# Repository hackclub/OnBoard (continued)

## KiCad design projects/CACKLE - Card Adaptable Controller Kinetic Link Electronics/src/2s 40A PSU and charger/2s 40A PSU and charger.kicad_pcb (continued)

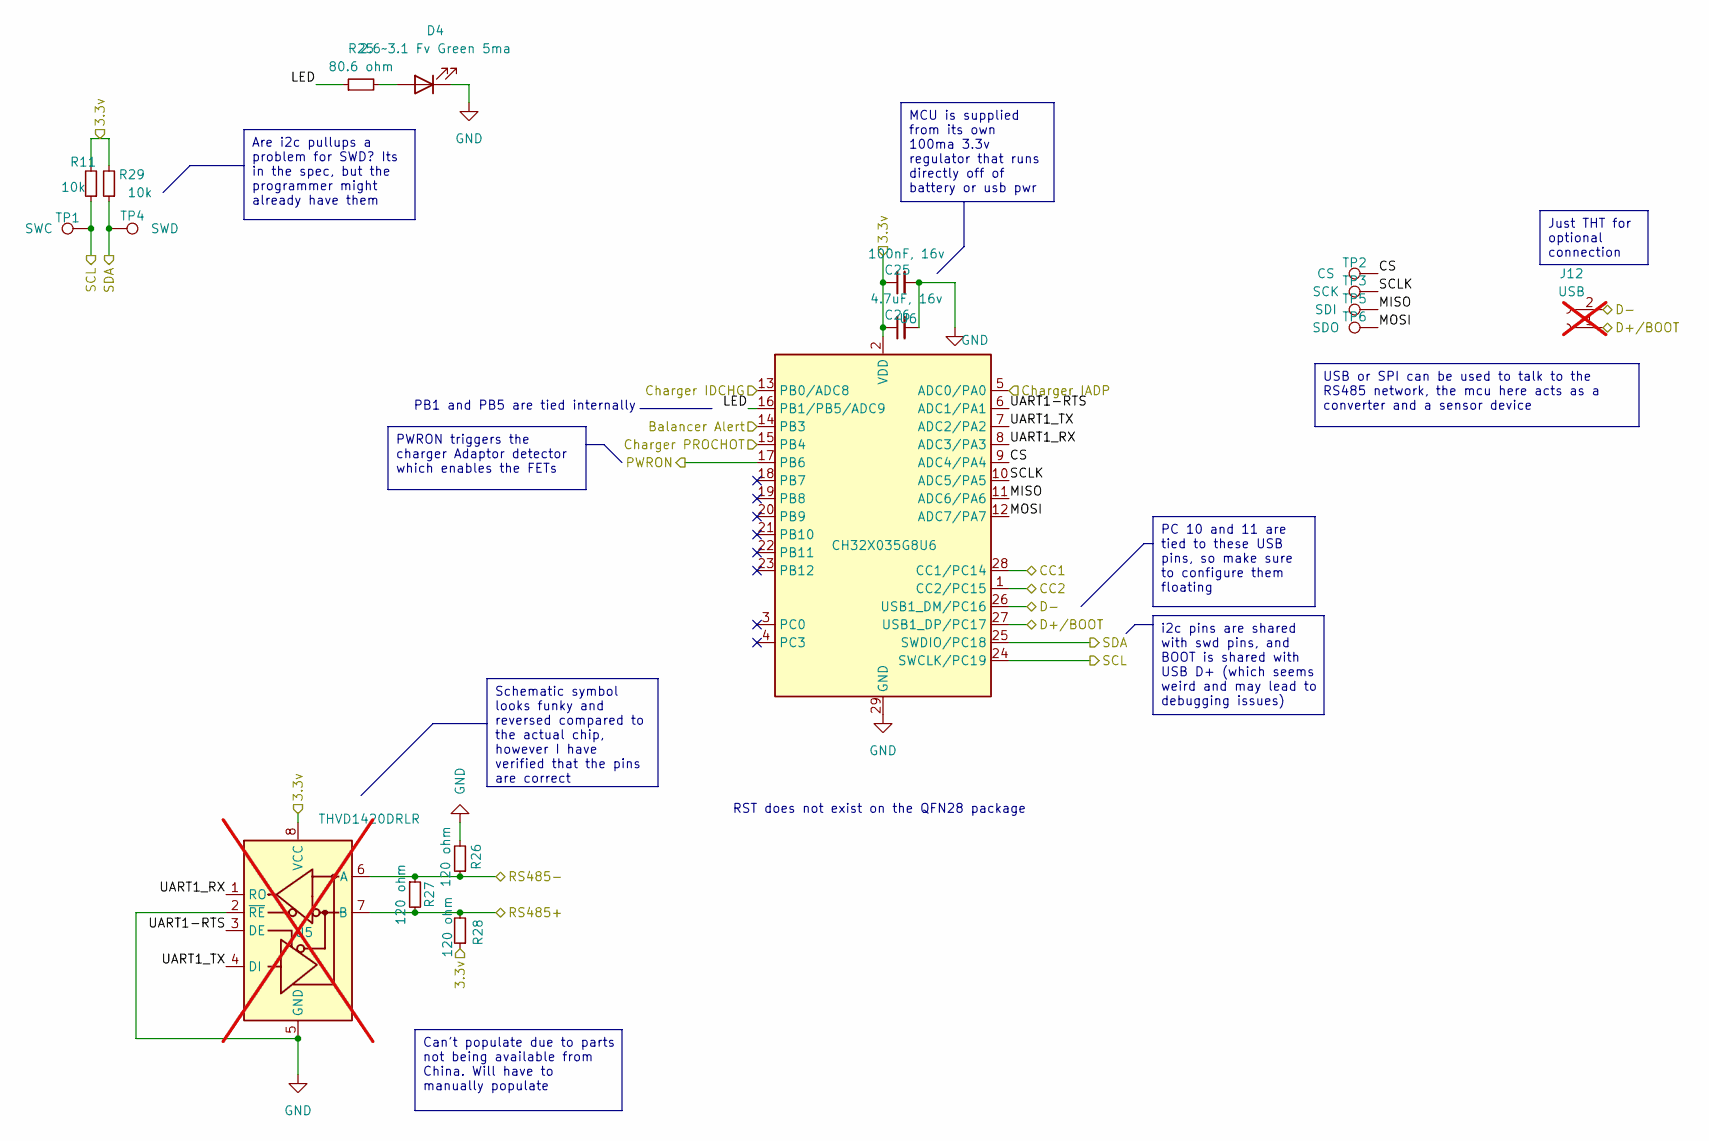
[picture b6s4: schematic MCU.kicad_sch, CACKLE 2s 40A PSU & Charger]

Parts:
C25: 100nF, 16v; C_0402_1005Metric; LCSC C1525
C26: 4.7uF, 16v; C_0603_1608Metric; LCSC C19666
D4: 2.6~3.1 Fv Green 5ma; LED_0603_1608Metric_Pad1.05x0.95mm_HandSolder; LCSC C3028858
J12: USB; PinHeader_1x02_P1.27mm_Vertical; not fitted
R11, R29: 10k; R_0402_1005Metric; LCSC C25744
R25: 80.6 ohm; R_0402_1005Metric; LCSC C185392
R26, R27, R28: 120 ohm; R_0402_1005Metric; LCSC C25079
TP1: SWC; TestPoint_Pad_D1.0mm
TP2: CS; TestPoint_Pad_D1.0mm
TP3: SCK; TestPoint_Pad_D1.0mm
TP4: SWD; TestPoint_Pad_D1.0mm
TP5: SDI; TestPoint_Pad_D1.0mm
TP6: SDO; TestPoint_Pad_D1.0mm
U5: THVD1420DRLR; SOT-583-8; not fitted
U6: CH32X035G8U6; QFN-28-1EP_4x4mm_P0.4mm_EP2.8x2.8mm; LCSC C7437027

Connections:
/Battery Balancer/Balancer Alert: U6.14 (PB3); also elsewhere on the board
/Battery Charger/Charger IADP: U6.5 (ADC0/PA0); also elsewhere on the board
/Battery Charger/Charger IDCHG: U6.13 (PB0/ADC8); also elsewhere on the board
/Battery Charger/Charger PROCHOT: U6.15 (PB4); also elsewhere on the board
/Battery Charger/MCU3.3v: C25.1, C26.1, R11.2, R28.1, R29.2, U5.8 (VCC), U6.2 (VDD); also elsewhere on the board
/Battery Charger/PWRON: U6.17 (PB6); also elsewhere on the board
/Connectors/CC1: U6.28 (CC1/PC14); also elsewhere on the board
/Connectors/CC2: U6.1 (CC2/PC15); also elsewhere on the board
/Connectors/D+: J12.1, U6.27 (USB1_DP/PC17); also elsewhere on the board
/Connectors/D-: J12.2, U6.26 (USB1_DM/PC16); also elsewhere on the board
/Connectors/RS485+: R27.2, R28.2, U5.7 (B); also elsewhere on the board
/Connectors/RS485-: R26.1, R27.1, U5.6 (A); also elsewhere on the board
/MCU/CS: TP2.1, U6.9 (ADC4/PA4)
/MCU/LED: R25.1, U6.16 (PB1/PB5/ADC9)
/MCU/MISO: TP5.1, U6.11 (ADC6/PA6)
/MCU/MOSI: TP6.1, U6.12 (ADC7/PA7)
/MCU/SCLK: TP3.1, U6.10 (ADC5/PA5)
/MCU/UART1-RTS: U5.3 (DE), U6.6 (ADC1/PA1)
/MCU/UART1_RX: U5.1 (RO), U6.8 (ADC3/PA3)
/MCU/UART1_TX: U5.4 (DI), U6.7 (ADC2/PA2)
/SCL: R11.1, TP1.1, U6.24 (SWCLK/PC19); also elsewhere on the board
/SDA: R29.1, TP4.1, U6.25 (SWDIO/PC18); also elsewhere on the board
GND: C25.2, C26.2, D4.1 (K), R26.2, U5.2 (~RE), U5.5 (GND), U6.29 (GND); also elsewhere on the board
unnamed: D4.2 (A), R25.2

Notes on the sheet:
i2c pins are shared with swd pins, and BOOT is shared with USB D+ (which seems weird and may lead to debugging issues)
MCU is supplied from its own 100ma 3.3v regulator that runs directly off of battery or usb pwr
USB or SPI can be used to talk to the RS485 network, the mcu here acts as a converter and a sensor device
Just THT for optional connection
PC 10 and 11 are tied to these USB pins, so make sure to configure them floating
PWRON triggers the charger Adaptor detector which enables the FETs
Can't populate due to parts not being available from China. Will have to manually populate
Schematic symbol looks funky and reversed compared to the actual chip, however I have verified that the pins are correct
Are i2c pullups a problem for SWD? Its in the spec, but the programmer might already have them
RST does not exist on the QFN28 package
PB1 and PB5 are tied internally

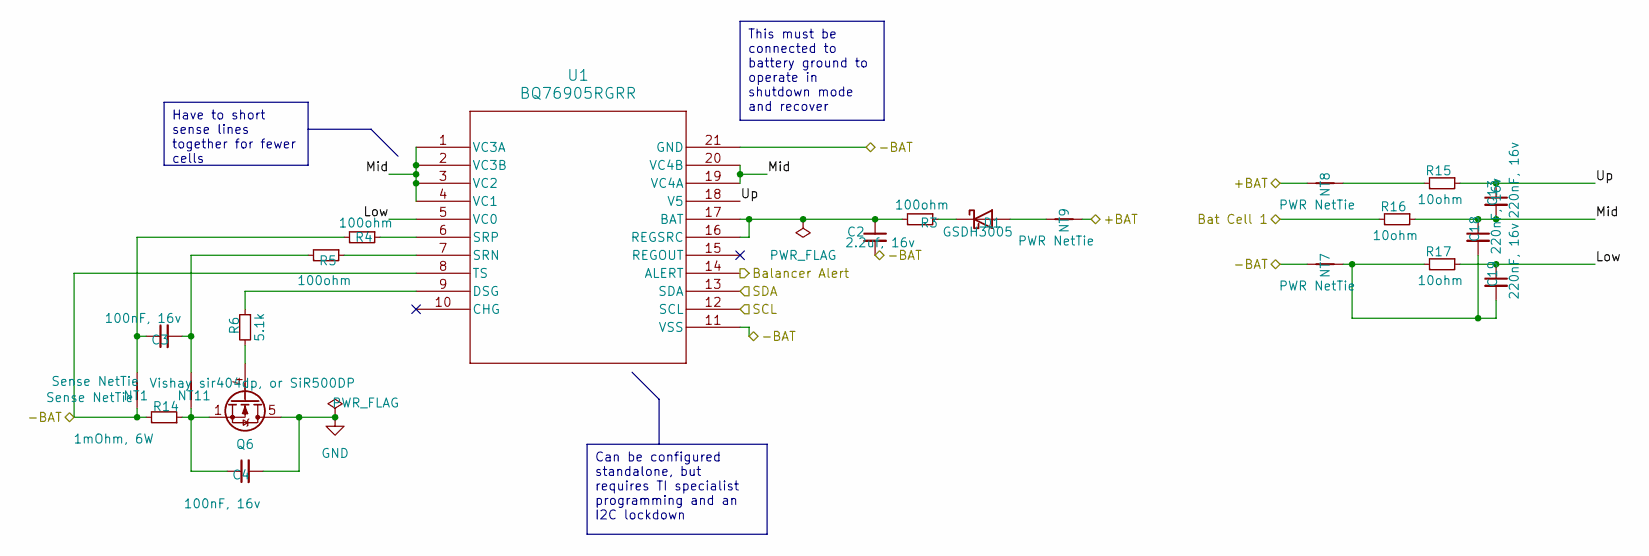
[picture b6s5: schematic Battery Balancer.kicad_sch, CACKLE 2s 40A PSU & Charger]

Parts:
C2: 2.2uf, 16v; C_0603_1608Metric; LCSC C23630
C3, C4: 100nF, 16v; C_0402_1005Metric; LCSC C1525
C13, C18, C19: 220nF, 16v; C_0402_1005Metric; LCSC C16772
D1: GSDH3005; D_0402_1005Metric; LCSC C2837790
NT1, NT11: Sense NetTie; NetTie-2_SMD_Pad0.2mm
NT7, NT8, NT9: PWR NetTie; NetTie-2_SMD_Pad0.28mm
Q6: Vishay sir404dp, or SiR500DP; PQFN-8-EP_6x5mm_P1.27mm_Generic; LCSC C3289487
R3, R4, R5: 100ohm; R_0402_1005Metric; LCSC C25076
R6: 5.1k; R_0402_1005Metric; LCSC C25905
R14: 1mOhm, 6W; R_2512_6332Metric_6W; LCSC C19270875
R15, R16, R17: 10ohm; R_0402_1005Metric; LCSC C25077
U1: BQ76905RGRR; VQFN20_RGR_TEX; LCSC C22394458

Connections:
/Battery Balancer/+BAT: NT8.2, NT9.1; also elsewhere on the board
/Battery Balancer/-BAT: C2.2, NT1.1, NT7.2, R14.2, U1.8 (TS), U1.11 (VSS), U1.21 (GND); also elsewhere on the board
/Battery Balancer/Balancer Alert: U1.14 (ALERT); also elsewhere on the board
/Battery Balancer/Bat Cell 1: R16.2; also elsewhere on the board
/Battery Balancer/Low: C19.1, R17.1, U1.5 (VC0)
/Battery Balancer/Mid: C13.2, C18.1, R16.1, U1.1 (VC3A), U1.2 (VC3B), U1.3 (VC2), U1.4 (VC1), U1.19 (VC4A), U1.20 (VC4B)
/Battery Balancer/Up: C13.1, R15.1, U1.18 (V5)
/SCL: U1.12 (SCL); also elsewhere on the board
/SDA: U1.13 (SDA); also elsewhere on the board
GND: C4.2, Q6.5 (D), Q6.6 (D), Q6.7 (D), Q6.8 (D); also elsewhere on the board
unnamed: C3.1, NT1.2, R4.2
unnamed: C3.2, NT11.2, R5.2
unnamed: C4.1, NT11.1, Q6.1 (S), Q6.2 (S), Q6.3 (S), R14.1
unnamed: C18.2, C19.2, NT7.1, R17.2
unnamed: D1.2 (A), NT9.2
unnamed: D1.1 (K), R3.1
unnamed: NT8.1, R15.2
unnamed: Q6.4 (G), R6.2
unnamed: C2.1, R3.2, U1.16 (REGSRC), U1.17 (BAT)
unnamed: R6.1, U1.9 (DSG)
unnamed: R5.1, U1.7 (SRN)
unnamed: R4.1, U1.6 (SRP)

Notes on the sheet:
This must be connected to battery ground to operate in shutdown mode and recover
Can be configured standalone, but requires TI specialist programming and an I2C lockdown
Have to short sense lines together for fewer cells

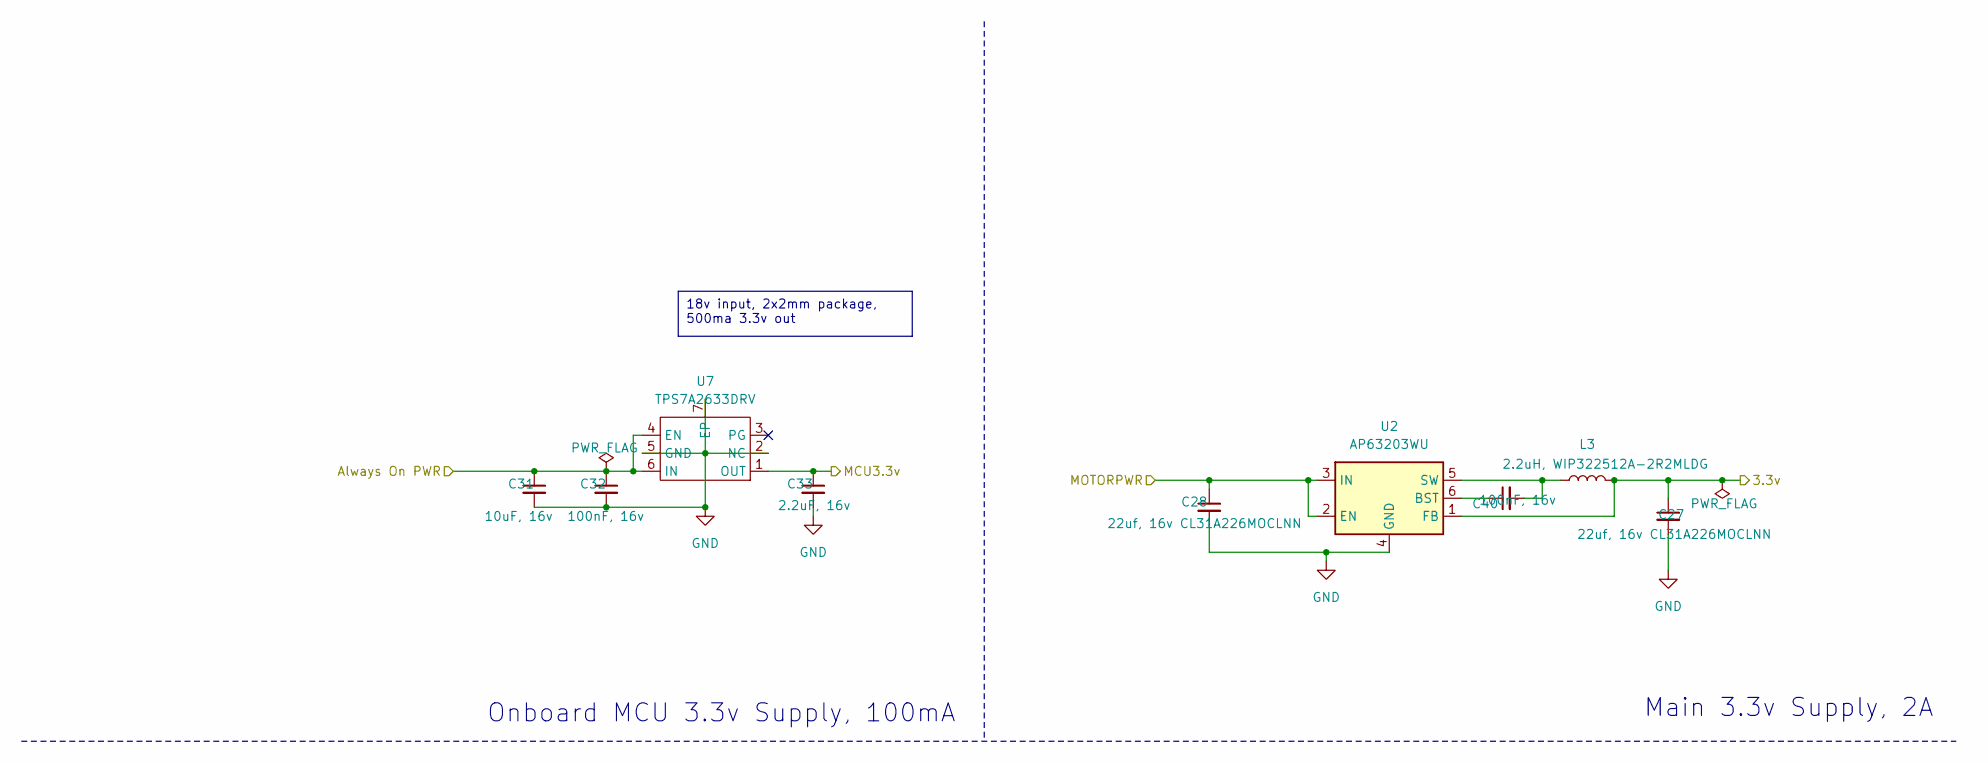
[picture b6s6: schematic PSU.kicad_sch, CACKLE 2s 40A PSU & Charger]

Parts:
C27, C28: 22uf, 16v CL31A226MOCLNN; C_1206_3216Metric; LCSC C159758
C31: 10uF, 16v; C_0603_1608Metric; LCSC C96446
C32: 100nF, 16v; C_0402_1005Metric; LCSC C1525
C33: 2.2uF, 16v; C_0402_1005Metric; LCSC C12530
C40: 100nF, 16v; C_0603_1608Metric; LCSC C14663
L3: 2.2uH, WIP322512A-2R2MLDG; L_1008_2520Metric; LCSC C5832372
U2: AP63203WU; TSOT-23-6; LCSC C780769
U7: TPS7A2633DRV; WSON-6-1EP_2x2mm_P0.65mm_EP1x1.6mm; LCSC C2876256

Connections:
/Battery Charger/Always On PWR: C31.1, C32.1, U7.4 (EN), U7.6 (IN); also elsewhere on the board
/Battery Charger/MCU3.3v: C33.1, U7.1 (OUT); also elsewhere on the board
/Battery Charger/MOTORPWR: C28.1, U2.2 (EN), U2.3 (IN); also elsewhere on the board
/Connectors/3.3v: C27.1, L3.2, U2.1 (FB); also elsewhere on the board
GND: C27.2, C28.2, C31.2, C32.2, C33.2, U2.4 (GND), U7.2 (NC), U7.5 (GND), U7.7 (EP); also elsewhere on the board
unnamed: C40.1, U2.6 (BST)
unnamed: C40.2, L3.1, U2.5 (SW)

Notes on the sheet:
18v input, 2x2mm package, 500ma 3.3v out
Onboard MCU 3.3v Supply, 100mA
Main 3.3v Supply, 2A

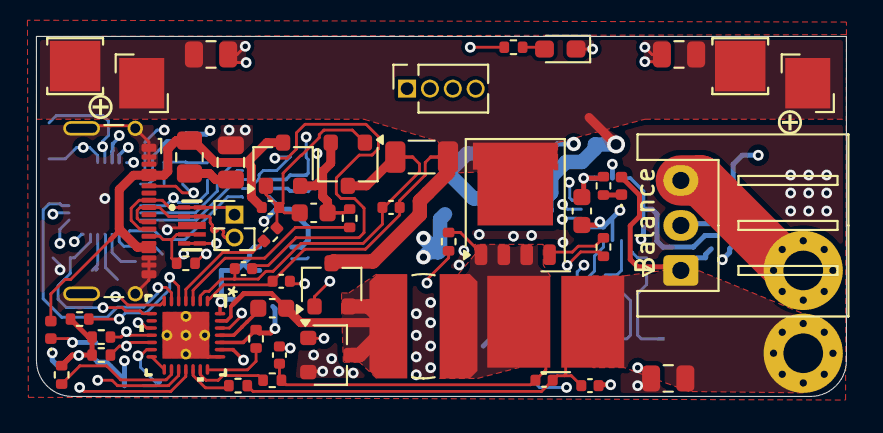
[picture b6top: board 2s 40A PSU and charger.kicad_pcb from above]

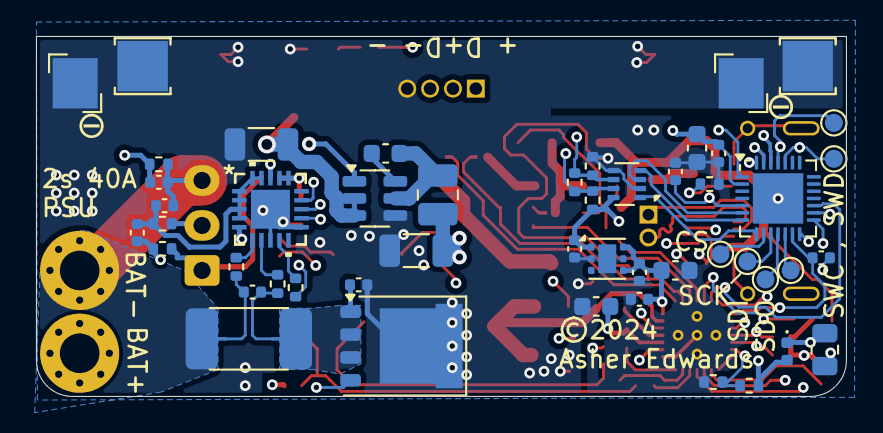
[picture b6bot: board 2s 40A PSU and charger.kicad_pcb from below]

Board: 4 copper layers, 45.0 x 20.0 mm, 112 parts (55 on the bottom side), 77 nets.

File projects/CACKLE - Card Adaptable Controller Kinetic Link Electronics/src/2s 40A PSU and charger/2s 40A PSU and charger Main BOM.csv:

"Id";"Designator";"Footprint";"Quantity";"Designation";"Supplier and ref";
1;"R14";"R_2512_6332Metric_6W";1;"1mOhm, 6W";;;
2;"R18";"R_Vishay_2818";1;"5mOhm, 10W, 2818";;;
3;"C9,C23,C10,C21,C11,C22,C32,C25,C4,C3";"C_0402_1005Metric";10;"100nF, 16v";;;
4;"D11";"CDDFN103324P";1;"CDDFN10-3324P";;;
5;"R24,R20,R23,R29,R11";"R_0402_1005Metric";5;"10k";;;
6;"R10,R8,R7";"R_0402_1005Metric";3;"4.02k";;;
7;"C20,C12,C7,C14";"C_0805_2012Metric";4;"10uF, 16v";;;
8;"R1";"R_1206_3216Metric";1;"10mOhm, 1W";;;
9;"Q1,Q5,Q4,Q2";"SC-59";4;"PJA3430, or HL 2320A";;;
10;"D1,D3,D2";"D_0402_1005Metric";3;"GSDH3005";;;
11;"R19,R6,R33";"R_0402_1005Metric";3;"5.1k";;;
12;"C2,C24";"C_0603_1608Metric";2;"2.2uf, 16v";;;
13;"R25";"R_0402_1005Metric";1;"80.6 ohm";;;
14;"C5";"C_0402_1005Metric";1;"1nF, 16v";;;
15;"J3,J1,J7,J6";"Keystone_3579";4;"Keystone 3579";;;
16;"R3,R5,R4";"R_0402_1005Metric";3;"100ohm";;;
17;"L2";"L_Bourns_SDR0604";1;"6.8uH HPC HPC5040NF-6R8M";;;
18;"J2";"JST_XH_S3B-XH-A_1x03_P2.50mm_Horizontal";1;"JST XH-S Balance Plug";;;
19;"J5,J4,J8,J9";"Keystone_3569_half";4;"Keystone 3569";;;
20;"J11";"PinSocket_1x04_P1.27mm_Vertical";1;"1.27mm 4 pin socket";;;
21;"R2";"R_0805_2012Metric";1;"2ohm";;;
22;"R21,R12,R22,R16,R17,R15";"R_0402_1005Metric";6;"10ohm";;;
23;"D4";"LED_0603_1608Metric_Pad1.05x0.95mm_HandSolder";1;"2.6~3.1 Fv Green 5ma";;;
24;"Q3,Q6";"PQFN-8-EP_6x5mm_P1.27mm_Generic";2;"Vishay sir404dp, or SiR500DP";;;
25;"U3";"RUY0028A";1;"BQ24780SRUYR";;;
26;"C6,C17";"C_0603_1608Metric";2;"47nF, 16v";;;
27;"J10";"USB_C_G-Switch_GT-USB-7025-JLCPCBv";1;"G-Switch-GT-USB-7025";;;
28;"R30,R31";"R_0402_1005Metric";2;"866k";;;
29;"U7";"WSON-6-1EP_2x2mm_P0.65mm_EP1x1.6mm";1;"TPS7A2633DRV";;;
30;"R26,R27,R28";"R_0402_1005Metric";3;"120 ohm";;;
31;"C15";"C_0402_1005Metric";1;"1uf, 16v";;;
32;"C28,C27";"C_1206_3216Metric";2;"22uf, 16v CL31A226MOCLNN";;;
33;"C31";"C_0603_1608Metric";1;"10uF, 16v";;;
34;"C40";"C_0603_1608Metric";1;"100nF, 16v";;;
35;"U5";"SOT-583-8";1;"THVD1420DRLR";;;
36;"C13,C19,C18";"C_0402_1005Metric";3;"220nF, 16v";;;
37;"L3";"L_1008_2520Metric";1;"2.2uH, WIP322512A-2R2MLDG";;;
38;"C30,C29";"C_0402_1005Metric";2;"100pF";;;
39;"C33";"C_0402_1005Metric";1;"2.2uF, 16v";;;
40;"U1";"VQFN20_RGR_TEX";1;"BQ76905RGRR";;;
41;"U6";"QFN-28-1EP_4x4mm_P0.4mm_EP2.8x2.8mm";1;"CH32X035G8U6";;;
42;"R9";"R_0805_2012Metric";1;"10ohm";;;
43;"U2";"TSOT-23-6";1;"AP63203WU";;;
44;"C26";"C_0603_1608Metric";1;"4.7uF, 16v";;;

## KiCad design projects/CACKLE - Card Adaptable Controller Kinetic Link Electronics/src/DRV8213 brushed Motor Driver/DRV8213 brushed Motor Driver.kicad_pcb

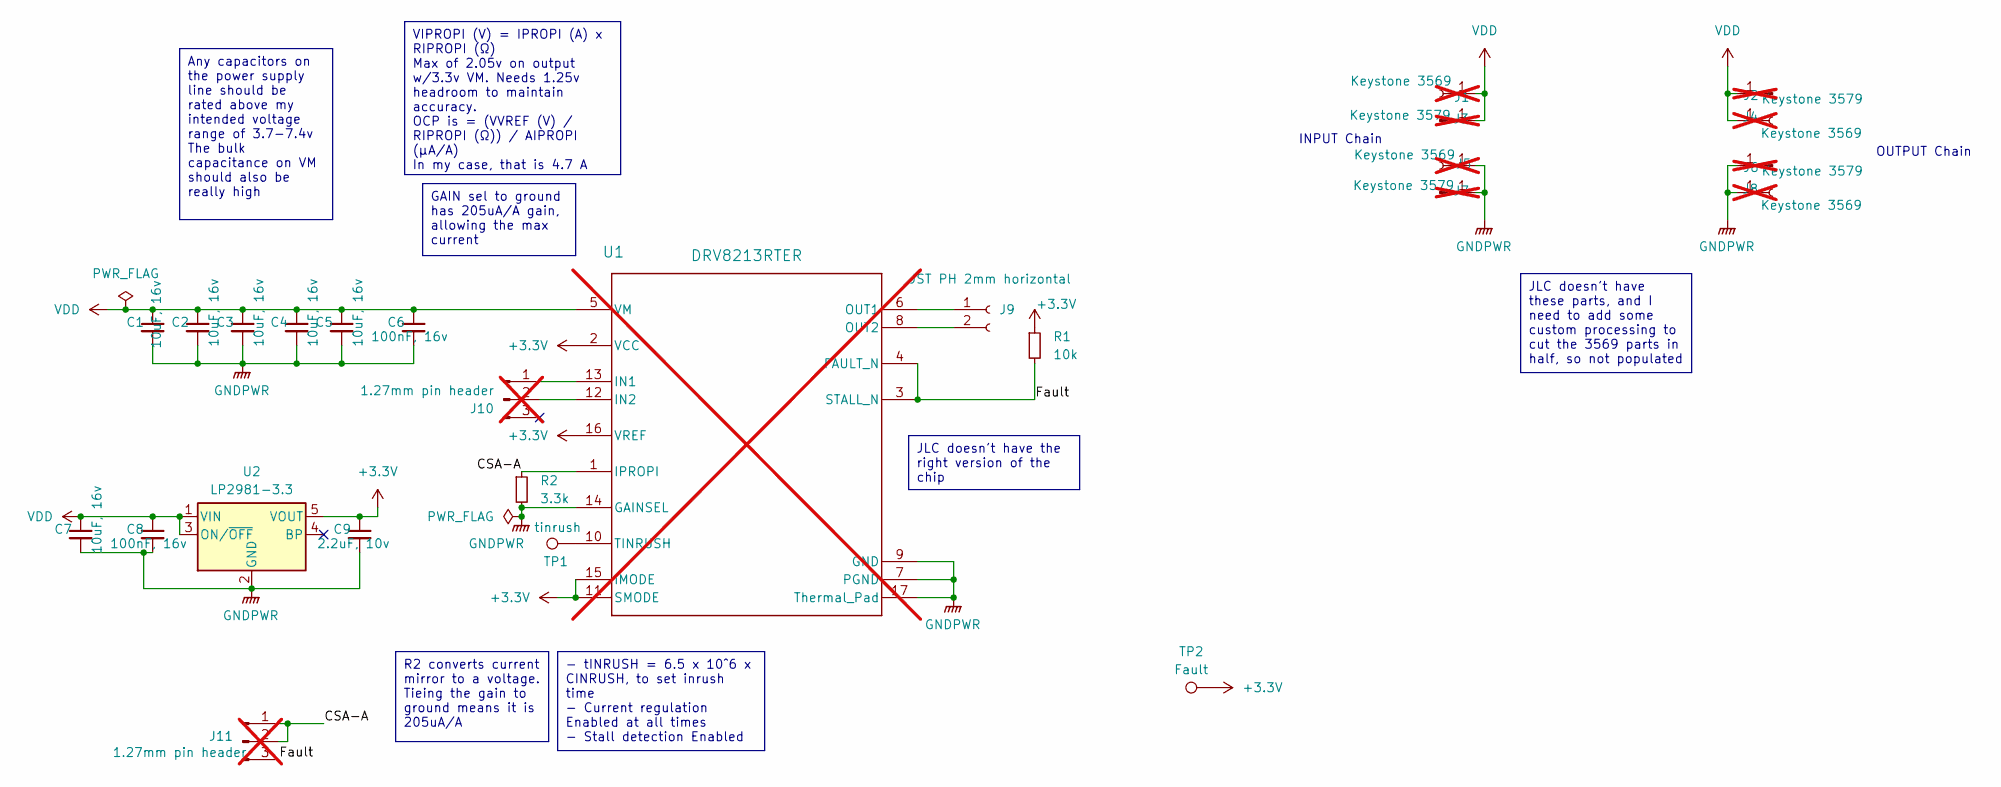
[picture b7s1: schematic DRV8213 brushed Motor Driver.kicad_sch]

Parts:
C1, C2, C3, C4, C5, C7: 10uF, 16v; C_0603_1608Metric; LCSC C96446
C6, C8: 100nF, 16v; C_0402_1005Metric; LCSC C1525
C9: 2.2uF, 10v; C_0402_1005Metric; LCSC C12530
J1, J4, J5, J8: Keystone 3569; Keystone_3569_half; not fitted
J2, J3, J6, J7: Keystone 3579; Keystone_3579; not fitted
J9: JST PH 2mm horizontal; JST_PH_S2B-PH-K_1x02_P2.00mm_Horizontal; LCSC C160237
J10, J11: 1.27mm pin header; PinHeader_1x03_P1.27mm_Horizontal; not fitted
R1: 10k; R_0402_1005Metric; LCSC C25744
R2: 3.3k; R_0402_1005Metric; LCSC C25890
TP1: tinrush; TestPoint_Pad_D1.0mm
TP2: Fault; TestPoint_Pad_D1.0mm
U1: DRV8213RTER; WQFN-16-1EP_3x3mm_P0.5mm_EP1.68x1.68mm_ThermalVias; not fitted
U2: LP2981-3.3; SOT-23-5; LCSC C129997

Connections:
+3.3V: C9.1, R1.1, TP2.1, U1.2 (VCC), U1.11 (SMODE), U1.15 (IMODE), U1.16 (VREF), U2.5 (VOUT)
/CSA-A: J11.1, J11.2, R2.1, U1.1 (IPROPI)
/Fault: J11.3, R1.2, U1.3 (STALL_N), U1.4 (FAULT_N)
GNDPWR: C1.2, C2.2, C3.2, C4.2, C5.2, C6.2, C7.2, C8.2, C9.2, J5.1, J6.1, J7.1, J8.1, R2.2, U1.7 (PGND), U1.9 (GND), U1.14 (GAINSEL), U1.17 (Thermal_Pad), U2.2 (GND)
unnamed: J9.1, U1.6 (OUT1)
unnamed: J9.2, U1.8 (OUT2)
unnamed: J10.1, U1.13 (IN1)
unnamed: J10.2, U1.12 (IN2)
unnamed: TP1.1, U1.10 (TINRUSH)
VDD: C1.1, C2.1, C3.1, C4.1, C5.1, C6.1, C7.1, C8.1, J1.1, J2.1, J3.1, J4.1, U1.5 (VM), U2.1 (VIN), U2.3 (ON/~OFF)

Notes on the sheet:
GAIN sel to ground has 205uA/A gain, allowing the max current
R2 converts current mirror to a voltage. Tieing the gain to ground means it is 205uA/A
VIPROPI (V) = IPROPI (A) x RIPROPI (Ω) Max of 2.05v on output w/3.3v VM. Needs 1.25v headroom to maintain accuracy. OCP is = (VVREF (V) / RIPROPI (Ω)) / AIPROPI (μA/A) In my case, that is 4.7 A
- tINRUSH = 6.5 x 10^6 x CINRUSH, to set inrush time - Current regulation Enabled at all times - Stall detection Enabled
JLC doesn't have these parts, and I need to add some custom processing to cut the 3569 parts in half, so not populated
JLC doesn't have the right version of the chip
Any capacitors on the power supply line should be rated above my intended voltage range of 3.7-7.4v The bulk capacitance on VM should also be really high
INPUT Chain
OUTPUT Chain

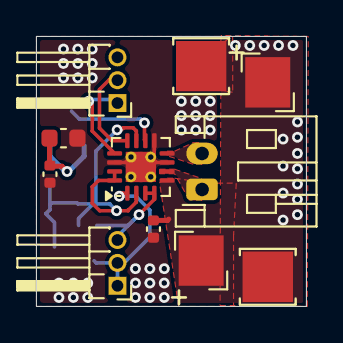
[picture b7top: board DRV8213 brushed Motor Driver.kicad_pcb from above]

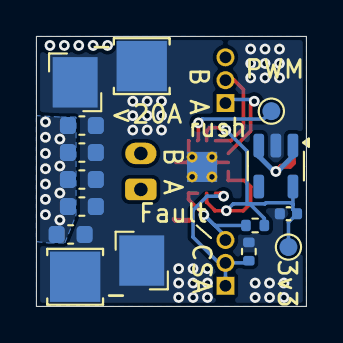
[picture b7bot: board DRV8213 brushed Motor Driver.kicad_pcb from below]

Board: 4 copper layers, 15.0 x 15.0 mm, 26 parts (15 on the bottom side), 10 nets.

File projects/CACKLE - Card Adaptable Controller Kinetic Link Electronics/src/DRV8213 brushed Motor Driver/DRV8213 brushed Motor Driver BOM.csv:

"Id";"Designator";"Footprint";"Quantity";"Designation";"Supplier and ref";
1;"J3,J2,J7,J6";"Keystone_3579";4;"Keystone 3579";;;
2;"J4,J1,J8,J5";"Keystone_3569_half";4;"Keystone 3569";;;
3;"C6,C8";"C_0402_1005Metric";2;"100nF, 16v";;;
4;"J11,J10";"PinHeader_1x03_P1.27mm_Horizontal";2;"1.27mm pin header";;;
5;"C7,C1,C4,C5,C3,C2";"C_0603_1608Metric";6;"10uF, 16v";;;
6;"J9";"JST_PH_S2B-PH-K_1x02_P2.00mm_Horizontal";1;"JST PH 2mm horizontal";;;
7;"U1";"WQFN-16-1EP_3x3mm_P0.5mm_EP1.68x1.68mm_ThermalVias";1;"DRV8213RTER";;;
8;"C9";"C_0402_1005Metric";1;"2.2uF, 10v";;;
9;"R2";"R_0402_1005Metric";1;"3.3k";;;
10;"U2";"SOT-23-5";1;"LP2981-3.3";;;
11;"R1";"R_0402_1005Metric";1;"10k";;;
